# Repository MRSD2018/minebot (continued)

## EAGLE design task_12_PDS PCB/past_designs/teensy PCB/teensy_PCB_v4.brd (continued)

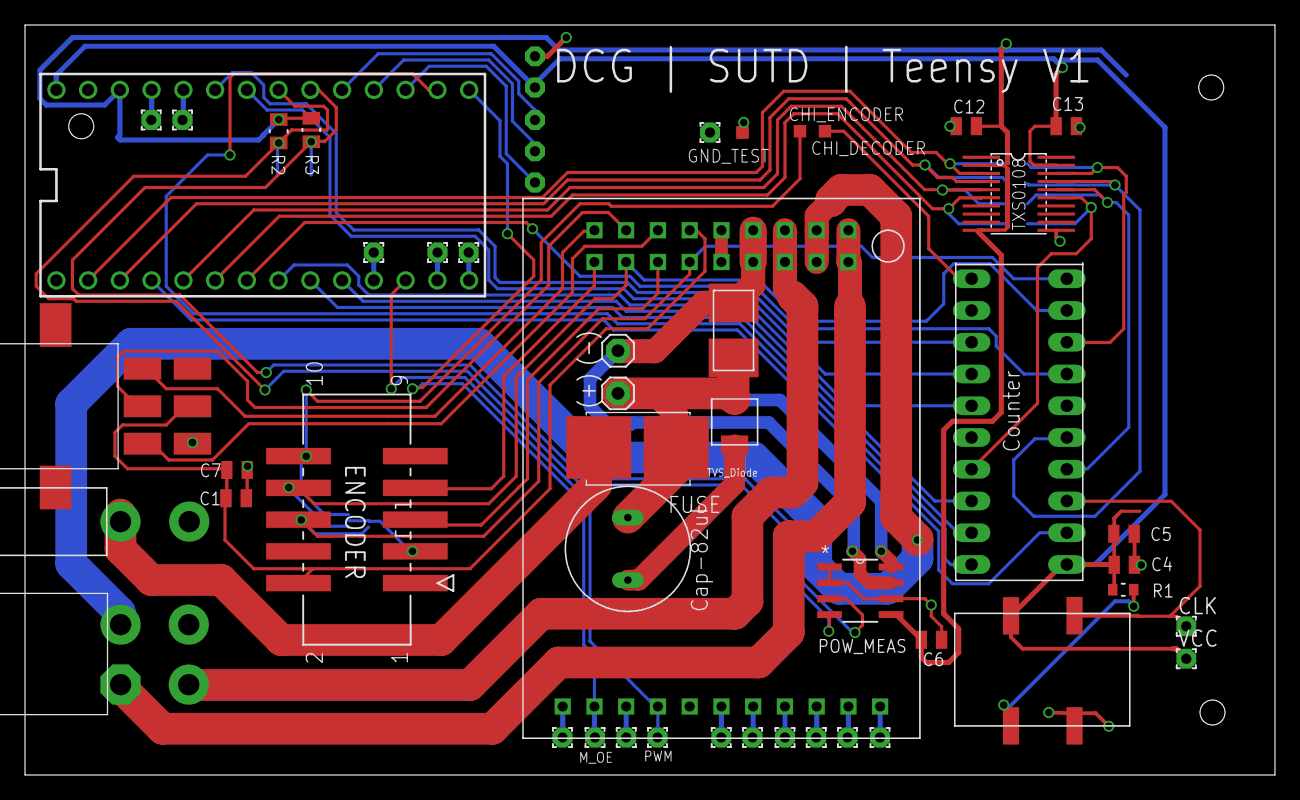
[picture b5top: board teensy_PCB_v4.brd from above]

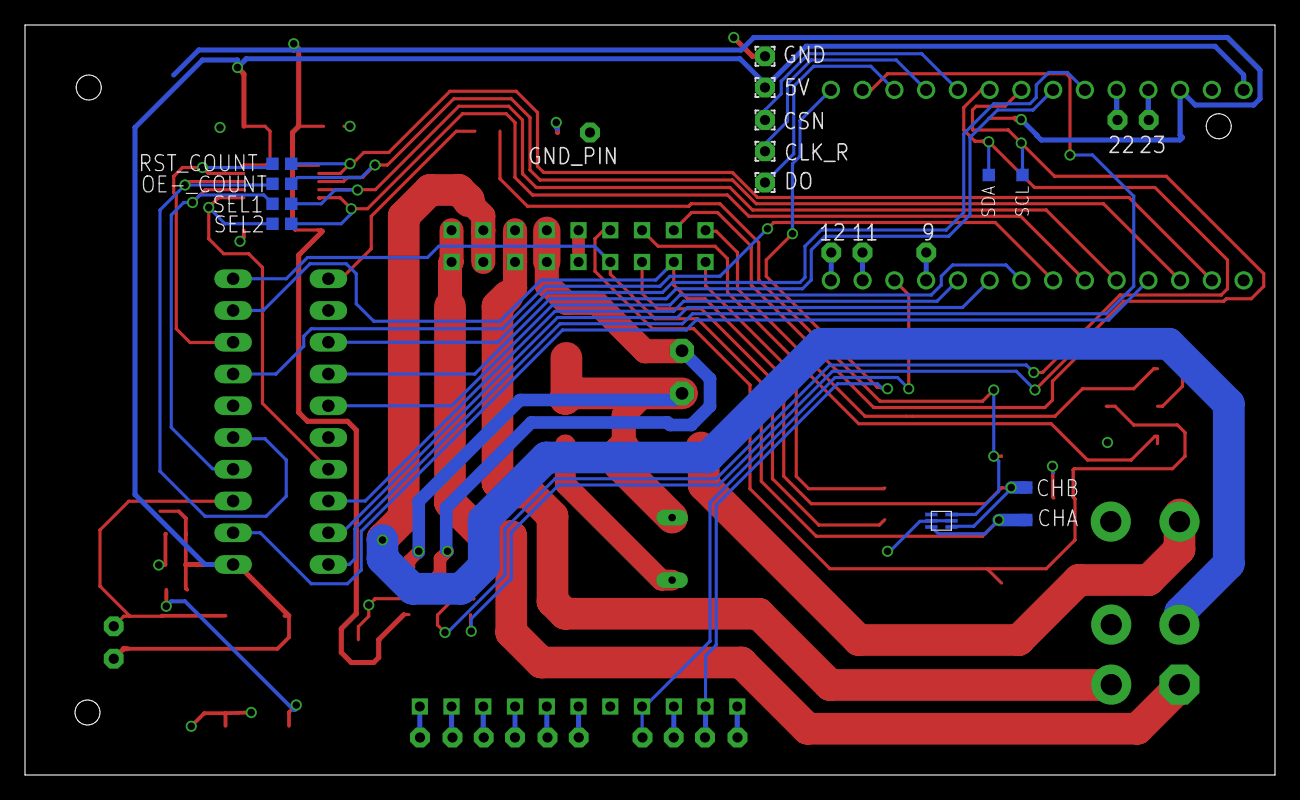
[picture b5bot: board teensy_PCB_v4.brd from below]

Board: 2 copper layers, 100.0 x 60.0 mm, 65 parts (18 on the bottom side), 57 nets.

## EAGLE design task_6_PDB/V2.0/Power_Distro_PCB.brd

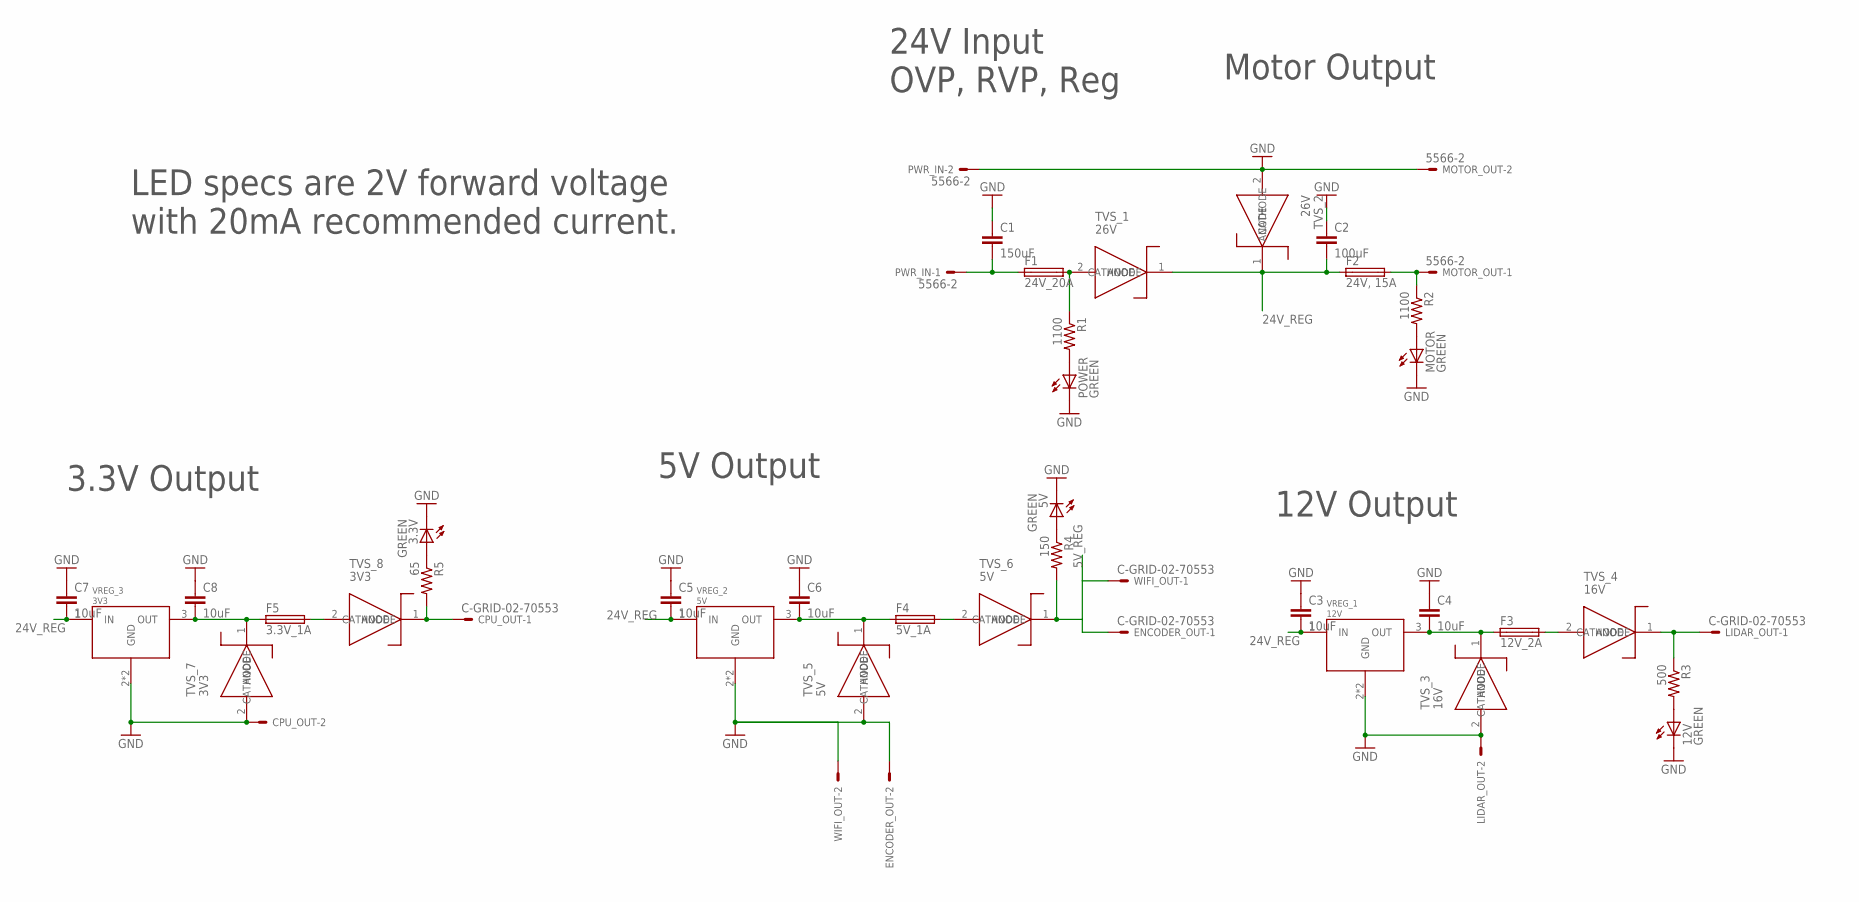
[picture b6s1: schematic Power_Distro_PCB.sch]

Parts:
3.3V, 5V, 12V: GREEN; SML1206
C1: 150uF; C1206
C2: 100uF; C1206
C3, C4, C5, C6, C7, C8: 10uF; C1206
CPU_OUT: C-GRID-02-70553; 70553-02
ENCODER_OUT: C-GRID-02-70553; 70553-02
F1: 24V_20A; TE5
F2: 24V, 15A; TE5
F3: 12V_2A; TE5
F4: 5V_1A; TE5
F5: 3.3V_1A; TE5
LIDAR_OUT: C-GRID-02-70553; 70553-02
MOTOR: GREEN; SML1206
MOTOR_OUT: 5566-2
POWER: GREEN; SML1206
PWR_IN: 5566-2
R1, R2: 1100; R1206
R3: 500; R1206
R4: 150; R1206
R5: 65; R1206
TVS_1, TVS_2: 26V; DO-214AC
TVS_3, TVS_4: 16V; DO-214AC
TVS_5, TVS_6: 5V; DO-214AC
TVS_7, TVS_8: 3V3; DO-214AA
VREG_1: 12V; TO-263-3
VREG_2: 5V; TO-263-3
VREG_3: 3V3; TO-263-3
WIFI_OUT: C-GRID-02-70553; 70553-02

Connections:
5V_REG: ENCODER_OUT.1, R4.2, TVS_6.1 (CATHODE), WIFI_OUT.1
12V_REG: LIDAR_OUT.1, R3.1, TVS_4.1 (CATHODE)
24V_REG: C2.2, C3.2, C5.2, C7.2, F2.1, TVS_1.1 (CATHODE), TVS_2.1 (CATHODE), VREG_1.1 (IN), VREG_2.1 (IN), VREG_3.1 (IN)
24V_REG_MOTOR: F2.2, MOTOR_OUT.1, R2.1
GND: 3.3V.C, 5V.C, 12V.C, C1.1, C2.1, C3.1, C4.1, C5.1, C6.1, C7.1, C8.1, CPU_OUT.2, ENCODER_OUT.2, LIDAR_OUT.2, MOTOR.C, MOTOR_OUT.2, POWER.C, PWR_IN.2, TVS_2.2 (ANODE), TVS_3.2 (ANODE), TVS_5.2 (ANODE), TVS_7.2 (ANODE), VREG_1.2 (GND), VREG_1.4 (GND), VREG_2.2 (GND), VREG_2.4 (GND), VREG_3.2 (GND), VREG_3.4 (GND), WIFI_OUT.2
unnamed: POWER.A, R1.2
unnamed: 12V.A, R3.2
unnamed: C1.2, F1.1, PWR_IN.1
unnamed: F5.2, TVS_8.2 (ANODE)
unnamed: CPU_OUT.1, R5.2, TVS_8.1 (CATHODE)
unnamed: C8.2, F5.1, TVS_7.1 (CATHODE), VREG_3.3 (OUT)
unnamed: C6.2, F4.1, TVS_5.1 (CATHODE), VREG_2.3 (OUT)
unnamed: MOTOR.A, R2.2
unnamed: F1.2, R1.1, TVS_1.2 (ANODE)
unnamed: C4.2, F3.1, TVS_3.1 (CATHODE), VREG_1.3 (OUT)
unnamed: F4.2, TVS_6.2 (ANODE)
unnamed: F3.2, TVS_4.2 (ANODE)
unnamed: 3.3V.A, R5.1
unnamed: 5V.A, R4.1

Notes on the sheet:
24V Input OVP, RVP, Reg
Motor Output
3.3V Output
5V Output
12V Output
LED specs are 2V forward voltage with 20mA recommended current.

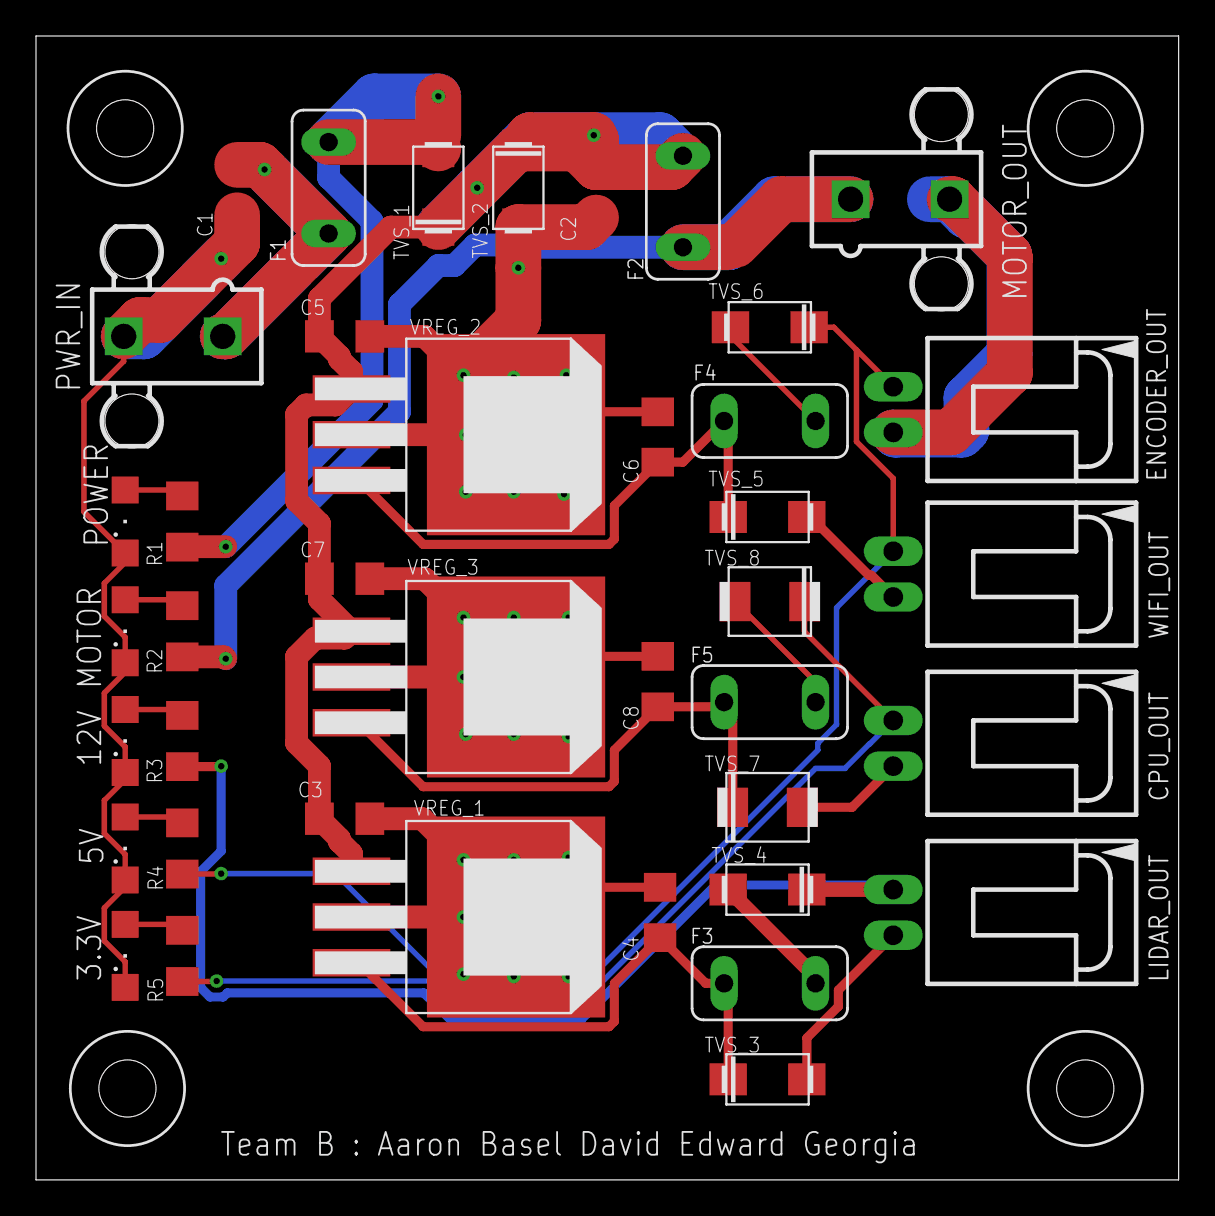
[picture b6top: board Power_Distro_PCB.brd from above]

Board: 2 copper layers, 63.5 x 63.6 mm, 40 parts (0 on the bottom side), 19 nets.

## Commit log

2017-10-04 layout done
2017-10-04 layout and labels done
2017-10-04 added 2D CAD models of board
2017-10-05 finished V2.0, corrected values and overall
2017-10-05 added notes for PDB layout
2017-10-06 updated CAD drawing
2017-10-06 motor vel control done
2017-10-06 changed name
2017-10-06 added analysis documents
2017-10-08 nothing much
2017-10-08 library added
2017-10-08 commented stuff
2017-10-08 changed direction
2017-10-08 finished motor lib
2017-10-08 initial gui commit
2017-10-08 added force sensor
2017-10-08 Added Servo_pot code
2017-10-08 Added pos_control w/ encoder counting
    Going back in to change to PID control
2017-10-08 aaron integrating code here
2017-10-09 Added Serial Communication & Plot Integration
2017-10-09 Added PD control for motor pos.
    Needs tuning and integration with RPM control
2017-10-09 gui layout updated
2017-10-09 Add skeleton code to run ir stepper
2017-10-09 Add libraries to run ir stepper code
2017-10-10 improve serial functions
2017-10-10 connected sensor plot
2017-10-10 tuned PID for DC motor position control
2017-10-10 refactored DC motor position PID control into a separate class - untested
2017-10-10 added DC motor velocity control - untested
2017-10-10 corrected syntax errors for previous commit but encoder counting not working
2017-10-10 Update infrared_stepper.ino
    now using enable pin
2017-10-10 Update ir_stepper.h
    now using enable pin
2017-10-10 DC motor pos and vel control complete
2017-10-10 main compiles fine
2017-10-10 added arduino serial interface for gui
2017-10-10 gui style changes
2017-10-11 added send command for manual input
2017-10-11 servo working in integrated code
2017-10-11 all motors working together
2017-10-11 added new library and stepperOnly code
2017-10-11 fixed stepper timer error
2017-10-11 added plotting capability for all motors
2017-10-11 all motors accept manual input
2017-10-11 added screenshots
2017-10-13 updated axis labels
2017-10-16 CAD for Horizontal Gantry
2017-10-17 Cleaned-up CAD folder
2017-10-17 probe assembly CAD models and drawings
2017-10-18 More clean-up
2017-10-20 revised probe-sensor assy design, with single shaft & bearing
2017-10-20 added dwg for load cell calibration mount assy
2017-10-20 imu ahrs, GPS nodes, encoder code PCB, old code
2017-10-20 sorry wrong folder for IMU code
2017-10-22 working publisher
2017-10-22 ASSN 12: PDB PCB Schematic
2017-10-23 put requirements under version control
2017-10-24 PCB sch done, added another lib called minebot_PDR.lbr
2017-10-24 added scorpion CAD wireframe and started on assy for probe actuation to gantry
2017-10-24 schematic finalized
2017-10-24 Added electrcal comp. mounts
2017-10-25 added user file
2017-10-25 added HX711 Library
2017-10-25 added plotting/logging qt gui
2017-10-25 added logging capability
2017-10-25 added logging functionality
2017-10-25 updated gantry CAD
2017-10-25 retrieving previously deleted files in load_cell_calibration
2017-10-26 fixed graph timing
2017-10-26 improved button functionality
2017-10-26 gantry and probing actuation CAD breakpoint
2017-10-26 create folders and readme
2017-10-26 added calibration script and data
2017-10-26 first probe data collection
2017-10-26 DC Motor Gantry Update
2017-10-27 visualization of subsurface probepoints
2017-10-28 improved axis labels
2017-10-28 merged PCB lbr
2017-10-28 MPU9250 working with teensy3.6 without AHRS
2017-10-30 5V switching regulators added
2017-10-30 calib and fusion done, results bad, probably IMU, gonna try my EM7180
2017-10-31 scorpion CAD complete for PDR
2017-10-31 Gantry Code updated for DC motor and driver
2017-11-01 PDB Updates
2017-11-01 PDB Board Updates
2017-11-02 Completed PDB Board
2017-11-02 Framework for speed/pos control for gantry
2017-11-03 added motor functionality
2017-11-04 added stepper interface
2017-11-05 added 3D printed parts and scripts for classification of circular objects
2017-11-07 PDB Final Updates
2017-11-07 added gerber based on slides
2017-11-08 Gantry Code and File Clean-up
2017-11-08 added zeroing functionality and state machine
2017-11-08 removed manual control functions
2017-11-08 added probing functionality
2017-11-08 Metal Detector Sweep Working
2017-11-08 generalized motor functions
2017-11-08 first attempt at ROS-uC communication
2017-11-08 continuing work on object classification code
2017-11-08 implemented a basic simulation of probing, not yet tested
2017-11-08 added entry to state functions
2017-11-09 added force limit to probe state
2017-11-09 added output for force logging
2017-11-09 Minor Gantry Sweep Tweeks
2017-11-10 updated load cell library
2017-11-13 Updating sweep code for teensy
2017-11-13 updated requirements to PDR level, CAD for limit switches, matlab script for circle fitting
2017-11-14 Gantry Control for Teensy
2017-11-14 Gantry commit to make myself feel good
2017-11-14 fixed teensy HX711 timing issue
2017-11-14 migrated probe control code to teensy
2017-11-14 Gantry File Clean-up
2017-11-15 added dc motor interface
2017-11-15 altered code for DC motor
2017-11-15 added force derivative
2017-11-15 new 3D printed parts and drill plate
2017-11-16 Wheel Encoder Mount and Plastic Gantry Legs
2017-11-16 fixed timing issue for HX711
2017-11-16 added calibration state
2017-11-16 added normalized force derivative threshold as object classifier
2017-11-17 Added ROS publisher for gantry
2017-11-18 Adjusted pins for brass board and indication LEDs
2017-11-20 mount design on husky done
2017-11-20 ROS publisher updated with correct POS
2017-11-21 migrated to protoboard
2017-11-23 updated protoboard
2017-11-25 Subscriber and Publiser Working!
2017-11-25 added seperate switch file
2017-11-26 CAD Updates (mostly electrical cases)
2017-11-26 Rotary Encoder Added to Gantry
2017-11-26 Renamed Metal_Detecting Folder
2017-11-27 FINALLY WORKING ... no state machine tho
2017-11-27 Metal Detector Working
2017-11-27 Upload md_vision code
2017-11-27 Additional md files
2017-12-16 End of semeseter clean-up
2018-01-21 added scorpion
2018-01-22 Removing CAD
2018-01-30 added hough transform
2018-01-30 refactoring
2018-02-06 PDB- production
2018-02-07 added PDB production files
2018-02-07 OK Things are back to normal situation normal everyone
2018-02-07 encoder PCB, sent for fab
2018-02-08 Routed PDB
2018-02-08 PDB fatter routes, dimension good, top ground plane
2018-02-10 Added initial planning sequence
2018-02-10 Updated PDB and Gerber files for US manufacturers
2018-02-11 finished probe sim for true +ves
2018-02-16 finished matlab planner simulation
2018-02-24 Gantry Motor Testing code
2018-02-24 Everything is AOK
2018-02-25 w/ positioning
2018-02-25 A hard day's work.
2018-03-02 Stepper Motor test code
2018-03-11 Gantry Main
2018-03-12 relay's implimented (no more crazy starts!!)
2018-03-19 Limit 22 not working
2018-03-19 Sweep Working
2018-03-19 E_stops implimented
2018-03-19 PID working for X and Y
2018-03-23 PID working (x is being weird)
2018-03-23 PDB missing route
2018-03-23 code from video
2018-03-25 speed funcion, cleaned-up PID, added testing fucntion
2018-03-25 debug implimented
2018-03-25 Added ROS cmds
2018-03-31 minor changes for added weight
2018-03-31 Ros msgs working
2018-04-02 gantry adjustments
